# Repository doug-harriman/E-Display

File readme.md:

# TO-DO

Updated: 2026-02-01

- [ ] Authentication through web page has not been updated for MSAL.

# Electronic Image Display Server

Image server for remote electronic displays such as a Kindle.

The image below shows my two devices, one displaying my work calendar in a portrait orientation, the other displaying the family calendar for the week in landscape.

|Server Pages|||
|-|-|-|
|||
|||

## Motivation

This project was motivated by two desires:
1. To have a nice display of my work calendar on my desk, available at a glance without having to open up Outlook.
2. To learn about web programming via Python.

I know there's a lot of stuff here that could be greatly improved.  Please submit pull requests if you'd like to help.

## Project Inspiration & References

There are many impressive projects out there that do similar things.  They've both inspired this project and provided great references for technical implementations.  Some great projects to check out:

* [Matt Healy's](https://matthealy.com/kindle) project was the one that originally inspired me.
    * I preferred to directly generate images for specific devices rather than generate web pages then convert to images.
    * He provides great instructions for the install process.  Great overview.
    * I'm still working on getting a frame like he has.
* A cuple of weather display projects that I really liked due to their use of weather icons:
    * [Weather Display](https://mpetroff.net/2012/09/kindle-weather-display/)
    * [Kindle Weather](https://github.com/DDRBoxman/kindle-weather)
        * SVG Files for weather icons, fonts too.
        * [Great example of managing Kindle services](https://github.com/DDRBoxman/kindle-weather/blob/master/kindleweather.sh).
* [A wall paper project](https://github.com/pablojimenezmateo/kindle-wallpaper)
    * Dumps the image file into the screensaver and reboots.
    * Sets a cron job to generate a new screen saver image once per day.
    * SVG files for weather icons.
* Two projects that dive deeper into reducing Kindle power usage:
    * [One with full power saving](https://github-com.translate.goog/nicoh88/kindle-kt3_weatherdisplay_battery-optimized?_x_tr_sl=auto&_x_tr_tl=en&_x_tr_hl=en)
    * [Another with power saving](https://www.martinpham.com/2023/01/07/reviving-unused-kindle-ebooks/)
* [A list of other Kindle projects from Mobileread](https://www.mobileread.com/forums/showthread.php?t=128704&highlight=wake+sleep+command).

## Key System Features

* Image generation performed on server to keep display device code as simple as possible.  This also allows for easy updates to the display without having to update the device.
* Server code constructed to support multiple display devices, so only a single server is needed.
* Display device can request sleep time from server, so that it can go into low power mode.  This allows the server to have complex logic to determine sleep duration based on a variety of factors.  I use it to reduce my work calendar display refresh rate during non-work hours.
    * Images are be pre-generated just ahead of wake time so that they're ready without wait mimimizing device battery usage.
* Display device can send basic state information (battery state of charge and local temperature) to server which is stored in an [SQLite3](https://www.sqlite.org/index.html) database.  State information can then be used for image generation.
* Server code constructed to support plugins, so features can be added easily and auto-discovered.

### Feature Details
* High-res image generation via [Pillow](https://pillow.readthedocs.io/en/stable/).
* Reusable image header and footer.
    * Header
        * Current day of week, month and date.
        * Battery state of charge.
    * Footer
        * Last update time (last time image was generated on server).
        * Device IP address.
        * Device name.
* Weather
    * Query weather forecast from USA National Weather Service.
    * Map weather forecast to icons.
* Google Calendar
    * Query events
    * Generate one week calendar image.
    * Select which of your Google calendars to display.
* Microsoft Outlook 365 Calendar
    * Query events
    * Generate hour by hour event image for the current day.
    * Display hour by hour weather forecast.
    * Request authentication URL from the web page, and apply the URL.  By default, some Outlook setups required admin approval for access longer than 24 hours.  This simplifies daily re-authentication.
* Custom string filters to remove unwanted text from event subjects for cleaner display.
* Display properties for Kindle Paperwhite
    * Screen resolution & size
    * Color maps (grayscale)
    * Fonts
* HTTP Post to MQTT Bridge
    * Post state information to MQTT broker.
    * Keeps device software simple.  MQTT data stream without adding MQTT client to device.
    * Additional small MQTT process to push MQTT data to Influx DB.
* Server software updates via `git pull` from direcltly from web server.

## Installation

The server should be set up and running before setting up the devices.  The devices will expect the server to be available so that they can pull images from it.

### Server

Installation and configuration for the server are covered in the [Server](server/readme.md) documentation.

### Kindle

Installation and configuration for using Kindle Paperwhite devices for an E-Display are covered in the [Kindle](kindle/readme.md) documentation.

## Creating a New Device Image

## Creating a New Plugin

## Next Tasks

- [ ] Server: Move all config/credential files to a single directory.
    - This would make it easier to sync files to the server.
    - Could then provide an upload/download functionality.
- [ ] Server: Family calendar image weather added
- [ ] Server: Review TODO's
- [ ] Server: Retrieve google cal events with async to speed up download of multiple calendars.
    - Google cal asyncio: https://pypi.org/project/aiogc/
    - Gathering results: https://superfastpython.com/asyncio-gather/#:~:text=main%20done-,Example%20of%20gather()%20With%20Return%20Values,-We%20may%20execute
- [ ] Server: Log to file.
- [ ] Server: renderer base should accept a layout parameter (landscape, portrait) and then manage resolution and image rotation internally.
- [ ] Server: Containerize to Docker.
- [ ] Server: Make MQTT2InfluxDB a daemon and run on container.
- [ ] Server: Icon updates.
    - Would be nice to have a battery outline icon to better match the weather icons.
    - During initial icon search, had trouble finding good SVG sets.  After battery icon was implemented found [Icônes](https://icones.js.org/), which has a lot of really good looking options.
        - From there, these look like good battery icon options:
            - https://icones.js.org/collection/mingcute?s=battery
            - https://icones.js.org/collection/typcn?s=battery
        - Potential weather changes
            - https://icones.js.org/collection/mdi?s=weather
            - https://icones.js.org/collection/uil?s=cloud

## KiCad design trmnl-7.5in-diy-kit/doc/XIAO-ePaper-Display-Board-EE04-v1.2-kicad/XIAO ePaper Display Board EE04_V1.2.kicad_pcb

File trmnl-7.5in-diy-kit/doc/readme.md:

# TRMNL 7.5" DIY Kit

## PCA Connections

## Reseting

To force a reset, hold the microswitch on the ESP daughterboard while pressing the reset button on the main board. There are two microswitches on the daughterboard.  The one for boot is closer to the battery plug.

## Links

* [Firmware GitHub](https://github.com/Seeed-Projects/Seeed_TRMNL_Eink_Project)
* [SEEED Studio Page](https://wiki.seeedstudio.com/trmnl_7inch5_diy_kit_main_page/)
* [SEEED Studio EE04 Display Board Page](https://wiki.seeedstudio.com/epaper_ee04/)
* [Overview Blog](https://www.seeedstudio.com/blog/2025/09/19/build-your-own-custom-e-ink-display-with-the-trmnl-diy-kit/)
* 3D Printed Enclosure Designs
   * [Triangular](https://www.printables.com/model/1354873-triangular-prism-3d-enclosure-for-trmnl-75-og-diy)
   * [L-Shaped](https://www.printables.com/model/1354879-l-shape-3d-enclosure-for-trmnl-75-og-diy-kit)

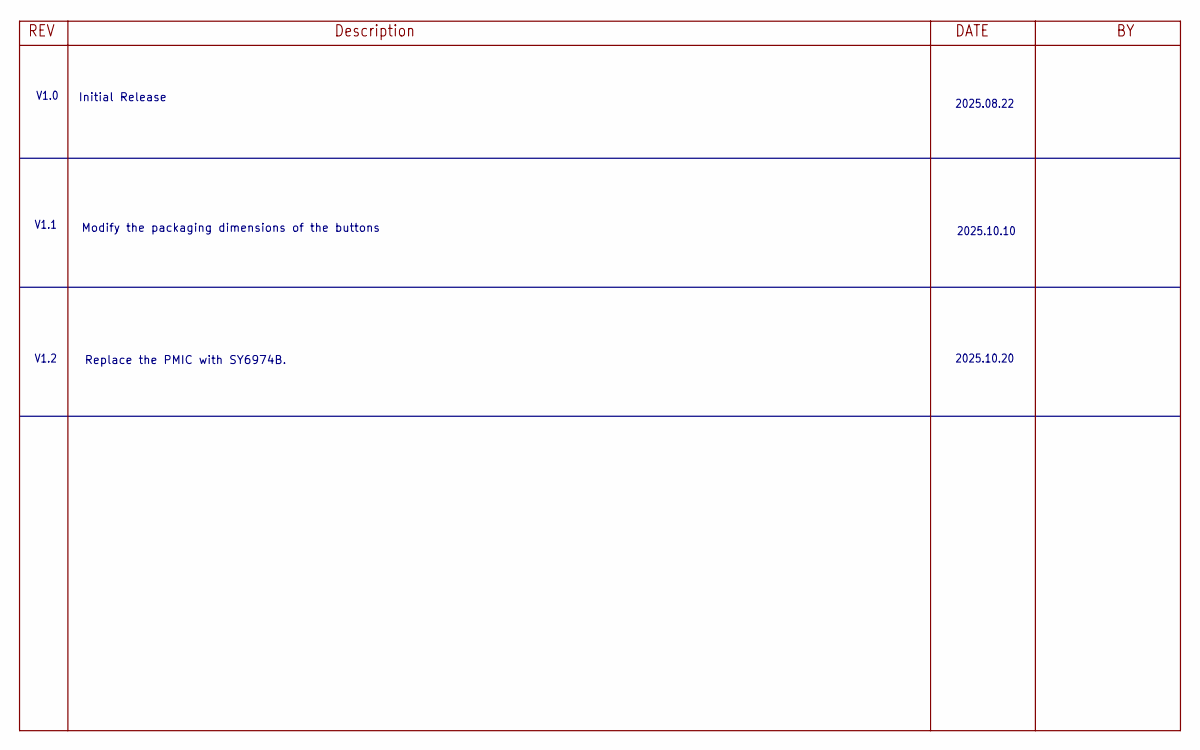
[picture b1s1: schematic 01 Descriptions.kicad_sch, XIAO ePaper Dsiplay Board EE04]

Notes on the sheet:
2025.08.22
2025.10.20
2025.10.10
Modify the packaging dimensions of the buttons
Replace the PMIC with SY6974B.
V1.1
Initial Release
V1.0
V1.2

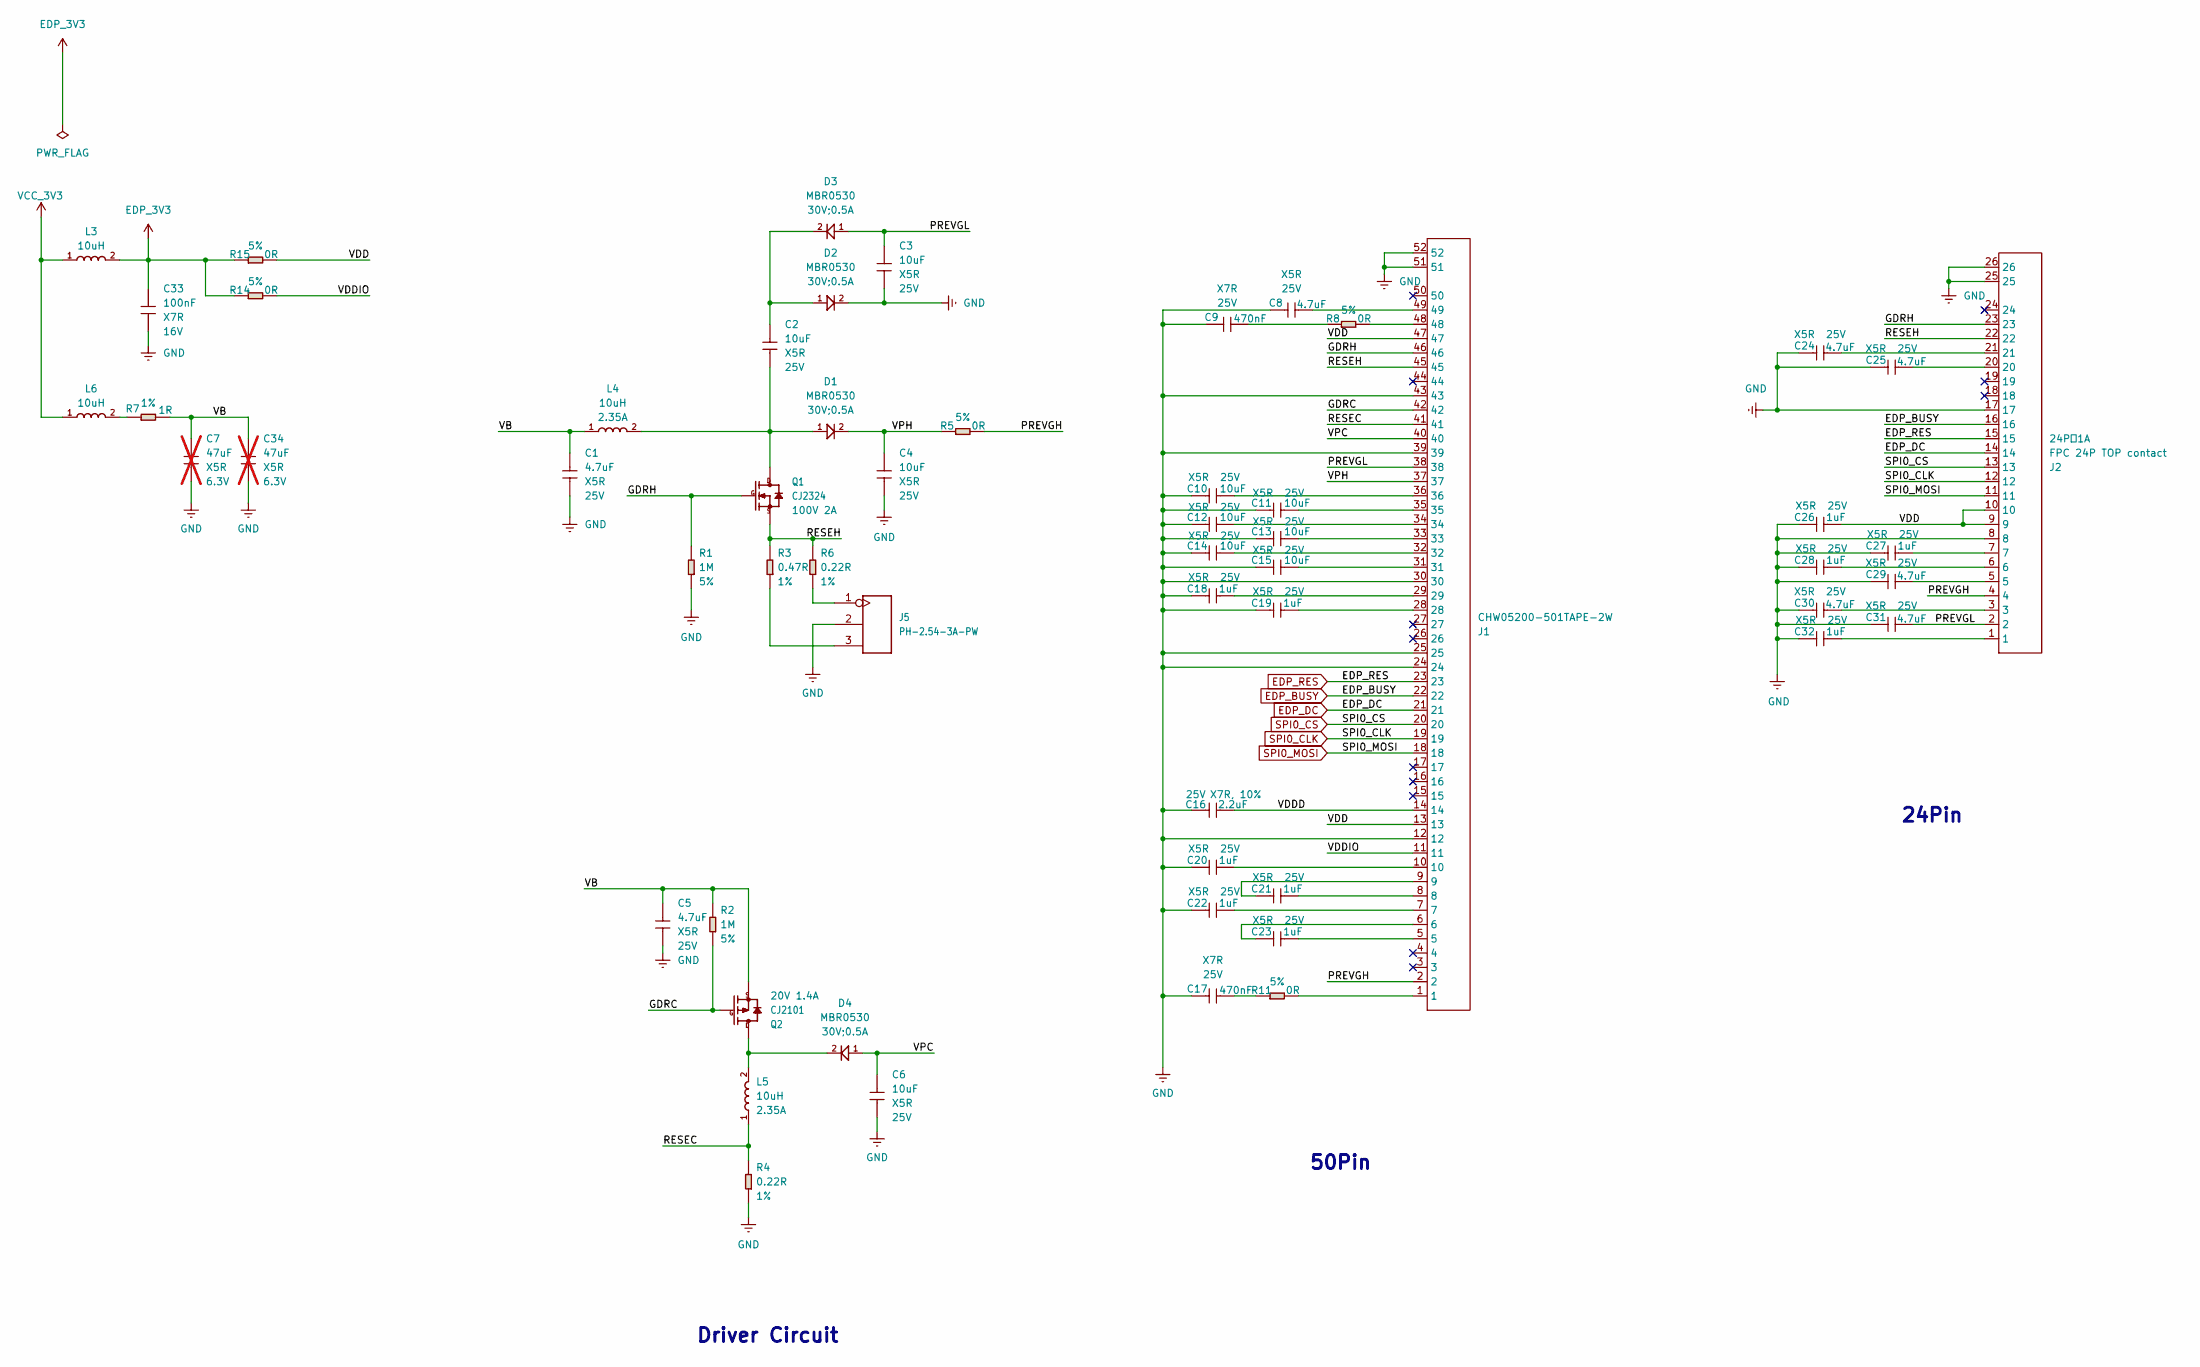
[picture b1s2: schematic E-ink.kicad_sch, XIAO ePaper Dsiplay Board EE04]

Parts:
C1, C5, C8, C24, C25, C29, C30, C31: 4.7uF; C0805; Voltage Rating 25V; MPN CC0805KKX5R8BB475
C2, C3, C4, C6, C10, C11, C12, C13, C14, C15: 10uF; C0805; Voltage Rating 25V; MPN CC0805KKX5R8BB106
C7, C34: 47uF; C0805; Voltage Rating 6.3V; MPN CC0805MKX5R5BB476; not fitted
C9, C17: 470nF; C0603; Voltage Rating 25V; MPN CC0603KRX7R8BB474
C16: 2.2uF; C0805; Voltage Rating 25V; MPN CC0805KKX7R8BB225
C18, C19, C20, C21, C22, C23, C26, C27, C28, C32: 1uF; C0402; Voltage Rating 25V; MPN CC0402KRX5R8BB105
C33: 100nF; C0402; Voltage Rating 16V; MPN CC0402KRX7R7BB104
D1, D2, D3, D4: MBR0530; SOD-123; Rating 30V;0.5A; MPN MBR0530
J1: CHW05200-501TAPE-2W; FPC50-0.5-28.6X4.9X2MM; MPN CHW05200-501TAPE-2W
J2: FPC 24P TOP contact; FPC24-0.5-15.5X4.9X2MM; Rating 24P，1A; MPN FPC0.5K-DH-24WB
J5: PH-2.54-3A-PW; H3-2.54-90D; MPN PH-2.54-3A-PW
L3, L6: 10uH; L0603; MPN MWSD1608FE100KT
L4, L5: 10uH; L5040S; Rating 2.35A; MPN SWPA5040S100MT
Q1: CJ2324; SOT23; Rating 100V 2A; MPN CJ2324
Q2: CJ2101; SOT-323; Rating 20V 1.4A; MPN CJ2101
R1, R2: 1M; R0402; Power Rating 5%; MPN RC0402JR-071ML
R3: 0.47R; R0603; Power Rating 1%; MPN RL0603FR-070R47L
R4, R6: 0.22R; R0805; Power Rating 1%; MPN RL0805FR-7W0R22L
R5, R8, R11, R14, R15: 0R; R0603; Power Rating 5%; MPN RC0603JR-070RL
R7: 1R; R0805; Power Rating 1%; MPN RC0805FR-071RL

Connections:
/E-ink/GDRC: J1.42, Q2.1 (G), R2.1
/E-ink/GDRH: J1.46, J2.23, Q1.1 (G), R1.2
/E-ink/PREVGH: J1.2, J2.4, R5.2
/E-ink/PREVGL: C3.2, C31.2, D3.1, J1.38, J2.2
/E-ink/RESEC: J1.41, L5.1, R4.2
/E-ink/RESEH: J1.45, J2.22, Q1.2 (S), R3.2, R6.2
/E-ink/VB: C1.1, C5.1, C7.1, C34.1, L4.1, Q2.2 (S), R2.2, R7.2
/E-ink/VDD: C26.2, J1.13, J1.47, J2.9, J2.10, R15.2
/E-ink/VDDD: C16.2, J1.14
/E-ink/VDDIO: J1.11, R14.2
/E-ink/VPC: C6.2, D4.1, J1.40
/E-ink/VPH: C4.2, D1.2, J1.37, R5.1
EDP_3V3: C33.1, L3.2, R14.1, R15.1
EDP_BUSY: J1.22, J2.16; also elsewhere on the board
EDP_DC: J1.21, J2.14; also elsewhere on the board
EDP_RES: J1.23, J2.15; also elsewhere on the board
GND: C1.2, C3.1, C4.1, C5.2, C6.1, C7.2, C8.1, C9.1, C10.2, C11.2, C12.2, C13.2, C14.2, C15.2, C16.1, C17.1, C18.1, C19.1, C20.1, C22.1, C24.1, C25.1, C26.1, C27.1, C28.1, C29.1, C30.1, C31.1, C32.1, C33.2, C34.2, D2.2, J1.12, J1.24, J1.25, J1.30, J1.39, J1.43, J1.51, J1.52, J2.8, J2.17, J2.25, J2.26, J5.2, R1.1, R4.1; also elsewhere on the board
unnamed: C2.2, D2.1, D3.2
unnamed: C8.2, J1.49
unnamed: C9.2, R8.1
unnamed: C10.1, J1.36
unnamed: C11.1, J1.35
unnamed: C12.1, J1.34
unnamed: C13.1, J1.33
unnamed: C14.1, J1.32
unnamed: C15.1, J1.31
unnamed: C17.2, R11.1
unnamed: C18.2, J1.29
unnamed: C19.2, J1.28
unnamed: C20.2, J1.10
unnamed: C21.1, J1.9
unnamed: C21.2, J1.8
unnamed: C22.2, J1.7
unnamed: C23.1, J1.6
unnamed: C23.2, J1.5
unnamed: C24.2, J2.21
unnamed: C25.2, J2.20
unnamed: C27.2, J2.7
unnamed: C28.2, J2.6
unnamed: C29.2, J2.5
unnamed: C30.2, J2.3
unnamed: C32.2, J2.1
unnamed: J1.1, R11.2
unnamed: J1.48, R8.2
unnamed: J5.1, R6.1
unnamed: J5.3, R3.1
unnamed: L6.2, R7.1
unnamed: C2.1, D1.1, L4.2, Q1.3 (D)
unnamed: D4.2, L5.2, Q2.3 (D)
SPI0_CLK: J1.19, J2.12; also elsewhere on the board
SPI0_CS: J1.20, J2.13; also elsewhere on the board
SPI0_MOSI: J1.18, J2.11; also elsewhere on the board
VCC_3V3: L3.1, L6.1; also elsewhere on the board

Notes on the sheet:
Driver Circuit
24Pin
50Pin

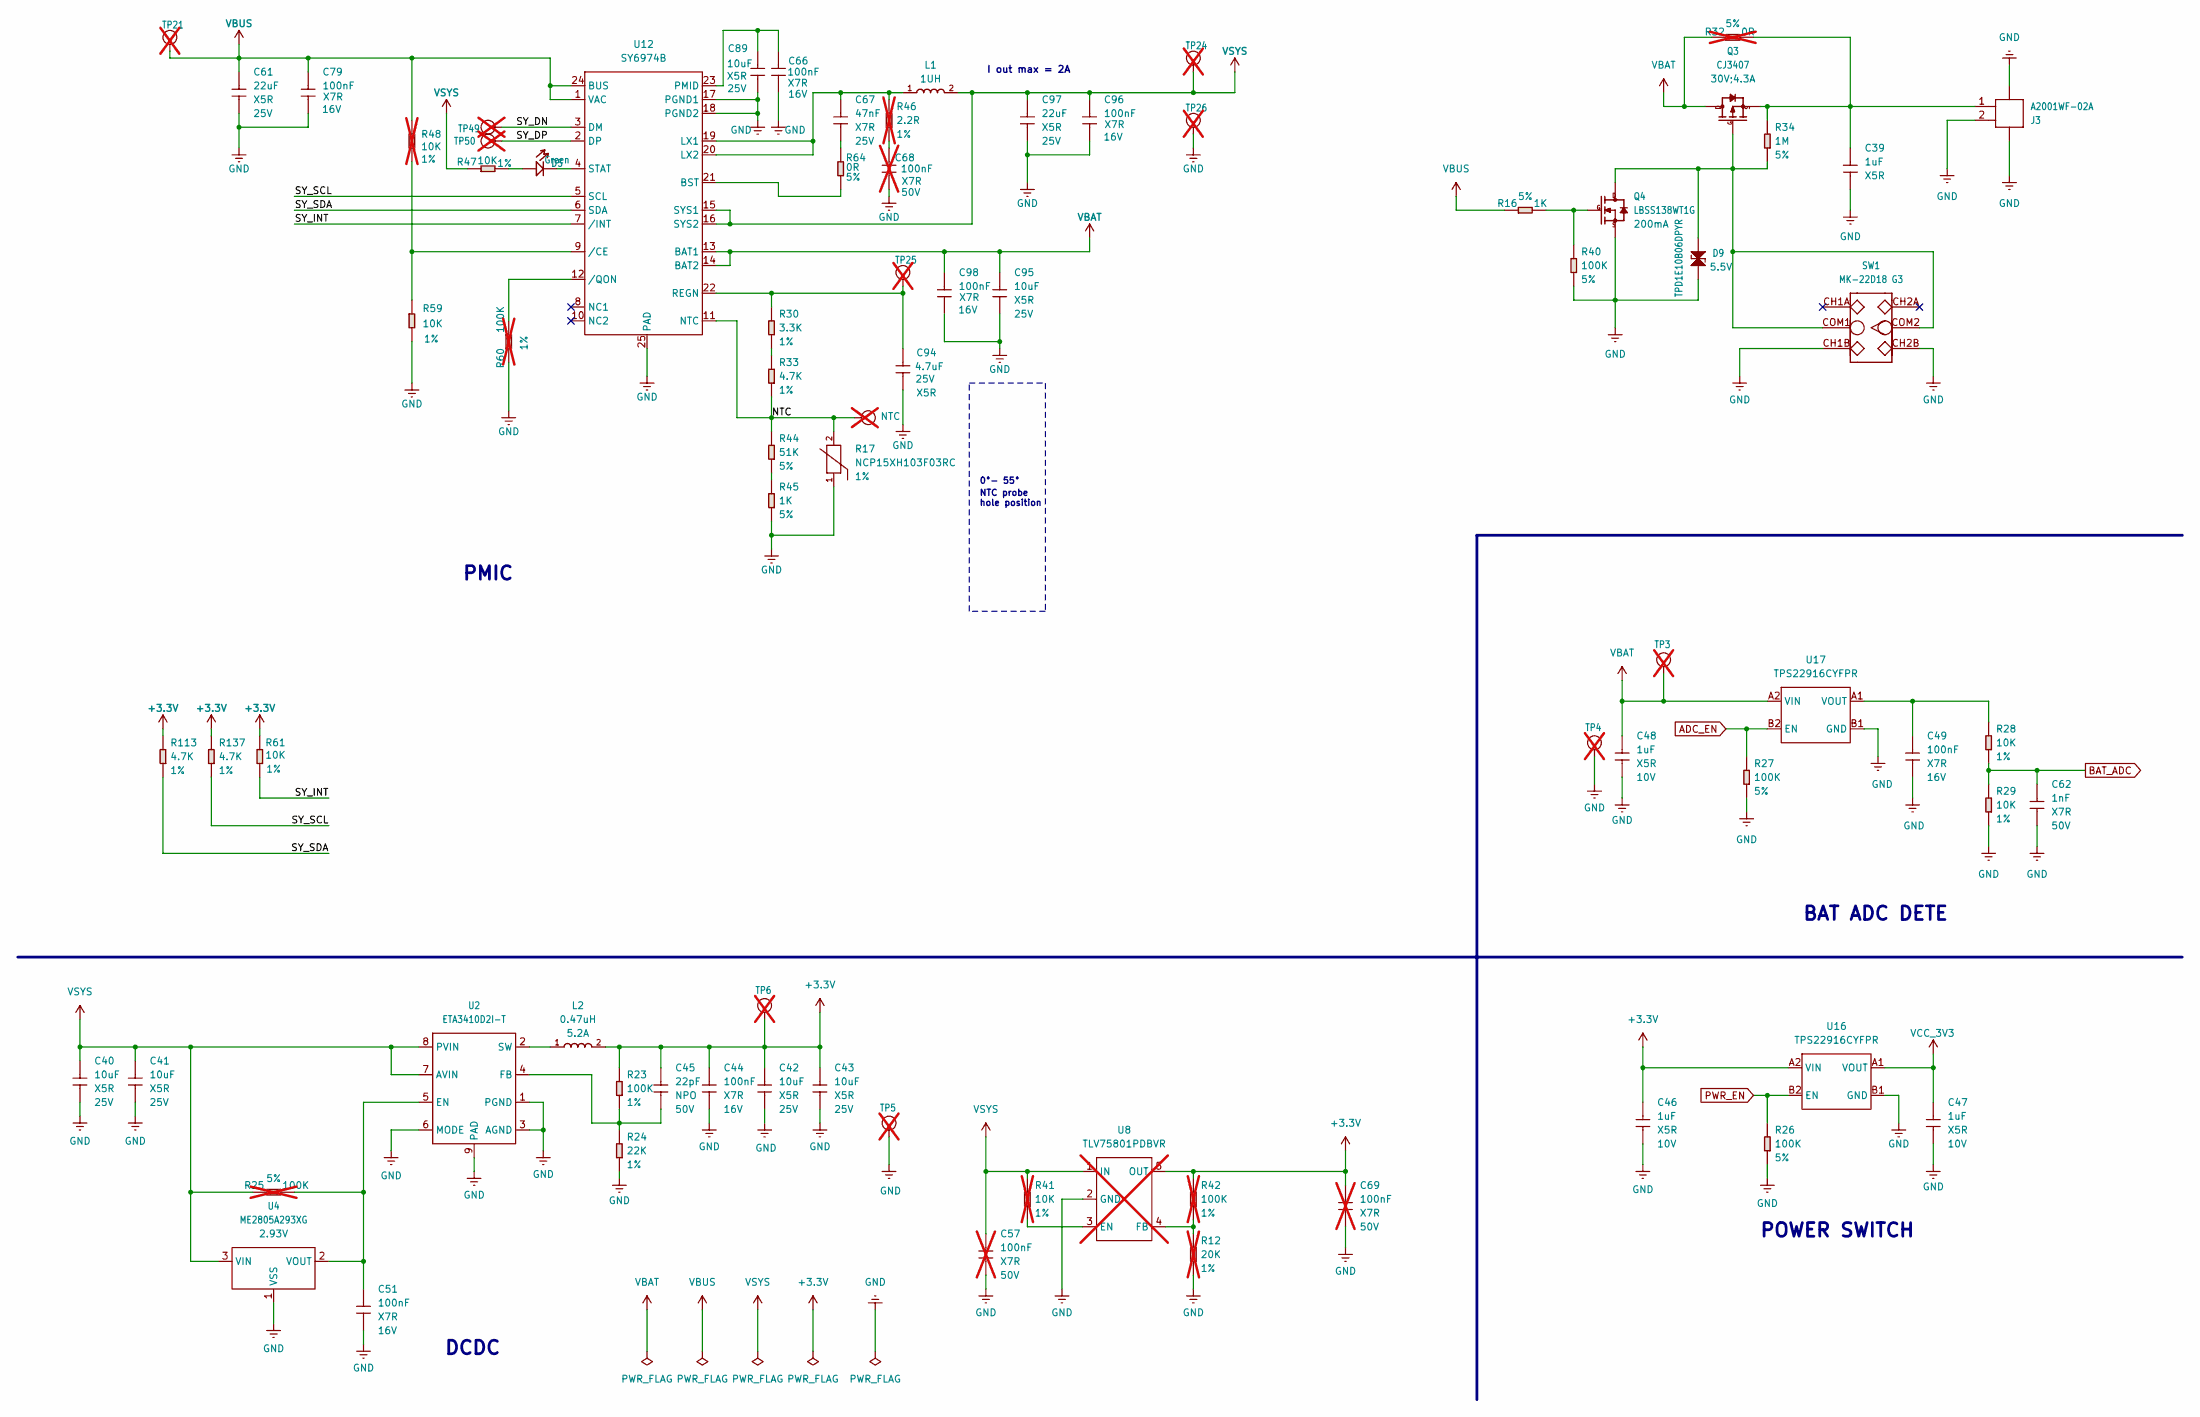
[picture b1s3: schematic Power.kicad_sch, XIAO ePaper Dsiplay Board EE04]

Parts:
C39, C46, C47, C48: 1uF; C0402; Voltage Rating 10V; MPN CC0402KRX5R6BB105
C40, C41, C42, C43, C89, C95: 10uF; C0805; Voltage Rating 25V; MPN CC0805KKX5R8BB106
C44, C49, C51, C66, C79, C96, C98: 100nF; C0402; Voltage Rating 16V; MPN CC0402KRX7R7BB104
C45: 22pF; C0402; Voltage Rating 50V; MPN CC0402JRNPO9BN220
C57, C68, C69: 100nF; C0603; Voltage Rating 50V; MPN CC0603KRX7R9BB104; not fitted
C61, C97: 22uF; C0805; Voltage Rating 25V; MPN CC0805MKX5R8BB226
C62: 1nF; C0402; Voltage Rating 50V; MPN CC0402KRX7R9BB102
C67: 47nF; C0402; Voltage Rating 25V; MPN CC0402KRX7R8BB473
C94: 4.7uF; C0805; Voltage Rating 25V; MPN CC0805KKX5R8BB475
D5: Green; LED2-0.6X1.7MM; MPN 27-21/GHC-YR1S2M/3C
D9: TPD1E10B06DPYR; ESD-0402; Rating 5.5V; MPN TPD1E10B06DPYR
J3: A2001WF-02A; JST2+2P_2.0_PH_S2B-PH-SM4-TB_1x02-1MP_Horizontal; MPN A2001WF-02A
L1: 1UH; INT2-SMD-4.2X4.4X1.8MM; MPN MWSA0402S-1R0MT
L2: 0.47uH; L0805; Rating 5.2A; MPN WPN201610MR47MT
NTC_IN2: NTC; TP-D45MIL; Part Type Test Point; not fitted
Q3: CJ3407; SOT23; Rating 30V;4.3A; MPN CJ3407
Q4: LBSS138WT1G; SOT-323; Rating 200mA; MPN LBSS138WT1G
R12: 20K; R0402; Power Rating 1%; MPN RC0402FR-0720KL; not fitted
R16, R45: 1K; R0402; Power Rating 5%; MPN RC0402JR-071KL
R17: NCP15XH103F03RC; R0402; Power Rating 1%; MPN NCP15XH103F03RC
R23: 100K; R0402; Power Rating 1%; MPN RC0402FR-07100KL
R24: 22K; R0402; Power Rating 1%; MPN RC0402FR-0722KL
R25: 100K; R0402; Power Rating 5%; MPN RC0402JR-07100KL; not fitted
R26, R27, R40: 100K; R0402; Power Rating 5%; MPN RC0402JR-07100KL
R28, R29, R47, R59, R61: 10K; R0402; Power Rating 1%; MPN RC0402FR-0710KL
R30: 3.3K; R0402; Power Rating 1%; MPN RC0402JR-073K3L
R32: 0R; R0603; Power Rating 5%; MPN RC0603JR-070RL; not fitted
R33, R113, R137: 4.7K; R0402; Power Rating 1%; MPN RC0402FR-074K7L
R34: 1M; R0402; Power Rating 5%; MPN RC0402JR-071ML
R41, R48: 10K; R0402; Power Rating 1%; MPN RC0402FR-0710KL; not fitted
R42, R60: 100K; R0402; Power Rating 1%; MPN RC0402FR-07100KL; not fitted
R44: 51K; R0402; Power Rating 5%; MPN RC0402JR-0751KL
R46: 2.2R; R0603; Power Rating 1%; MPN RC0603FR-072R2L; not fitted
R64: 0R; R0402; Power Rating 5%; MPN RC0402JR-070RL
SW1: MK-22D18 G3; SW6-2CH-2.54-9X3.5X3.5; MPN MK-22D18 G3
TP3, TP4, TP5, TP6, TP21, TP24, TP25, TP26, TP49, TP50: Test Point; TP-D45MIL; Part Type Test Point; not fitted
U2: ETA3410D2I-T; DFN8G-0.5-2X2MM; MPN ETA3410D2I-T
U4: ME2805A293XG; SOT-23; Rating 2.93V; MPN ME2805A293XG
U8: TLV75801PDBVR; SOT-23-5; MPN TLV75801PDBVR; not fitted
U12: SY6974B; QFN24G-0.5-4X4MM; MPN SY6974B
U16, U17: TPS22916CYFPR; WLCSP4-0.4-0.77X0.77X0.33MM; MPN TPS22916CYFPR

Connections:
+3.3V: C42.2, C43.2, C44.1, C45.1, C46.1, C69.1, L2.2, R23.2, R42.2, R61.2, R113.2, R137.2, TP6.1 (T), U8.5 (OUT), U16.A2 (VIN)
/Power/NTC: NTC_IN2.1 (T), R17.2, R33.1, R44.2, U12.11 (NTC)
/Power/SY_DN: TP49.1 (T), U12.3 (DM)
/Power/SY_DP: TP50.1 (T), U12.2 (DP)
/Power/SY_INT: R61.1, U12.7 (/INT)
/Power/SY_SCL: R137.1, U12.5 (SCL)
/Power/SY_SDA: R113.1, U12.6 (SDA)
ADC_EN: R27.2, U17.B2 (EN); also elsewhere on the board
BAT_ADC: C62.1, R28.1, R29.2; also elsewhere on the board
GND: C39.2, C40.1, C41.1, C42.1, C43.1, C44.2, C46.2, C47.2, C48.2, C49.2, C51.2, C57.2, C61.2, C62.2, C66.1, C68.1, C69.2, C79.2, C89.1, C94.2, C95.2, C96.2, C97.2, C98.2, D9.1, J3.2, J3.3, J3.4, Q4.2 (S), R12.1, R17.1, R24.1, R26.1, R27.1, R29.1, R40.1, R45.1, R59.2, R60.2, SW1.CH1B, SW1.CH2B, TP4.1 (T), TP5.1 (T), TP26.1 (T), U2.1 (PGND), U2.3 (AGND), U2.6 (MODE), U2.9 (PAD), U4.1 (VSS), U8.2 (GND), U12.17 (PGND1), U12.18 (PGND2), U12.25 (PAD), U16.B1 (GND), U17.B1 (GND); also elsewhere on the board
unnamed: C67.2, R64.2
unnamed: C68.2, R46.1
unnamed: D5.1 (+), R47.2
unnamed: D5.2 (-), U12.4 (STAT)
unnamed: D9.2, Q3.1 (G), Q4.3 (D), R34.1, SW1.COM1, SW1.COM2
unnamed: C39.1, J3.1, Q3.2 (S), R32.2, R34.2
unnamed: Q4.1 (G), R16.2, R40.2
unnamed: R30.1, R33.2
unnamed: R44.1, R45.2
unnamed: C94.1, R30.2, TP25.1 (T), U12.22 (REGN)
unnamed: C51.1, R25.1, U2.5 (EN), U4.2 (VOUT)
unnamed: C45.2, R23.1, R24.2, U2.4 (FB)
unnamed: L2.1, U2.2 (SW)
unnamed: R41.1, U8.3 (EN)
unnamed: R12.2, R42.1, U8.4 (FB)
unnamed: R64.1, U12.21 (BST)
unnamed: C67.1, L1.1, R46.2, U12.19 (LX1), U12.20 (LX2)
unnamed: C66.2, C89.2, U12.23 (PMID)
unnamed: R48.1, R59.1, U12.9 (/CE)
unnamed: R60.1, U12.12 (/QON)
unnamed: C49.1, R28.2, U17.A1 (VOUT)
PWR_EN: R26.2, U16.B2 (EN); also elsewhere on the board
VBAT: C48.1, C95.1, C98.1, Q3.3 (D), R32.1, TP3.1 (T), U12.13 (BAT1), U12.14 (BAT2), U17.A2 (VIN); also elsewhere on the board
VBUS: C61.1, C79.1, R16.1, R48.2, TP21.1 (T), U12.1 (VAC), U12.24 (BUS); also elsewhere on the board
VCC_3V3: C47.1, U16.A1 (VOUT); also elsewhere on the board
VSYS: C40.2, C41.2, C57.1, C96.1, C97.1, L1.2, R25.2, R41.2, R47.1, TP24.1 (T), U2.7 (AVIN), U2.8 (PVIN), U4.3 (VIN), U8.1 (IN), U12.15 (SYS1), U12.16 (SYS2)

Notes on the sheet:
PMIC
DCDC
BAT ADC DETE
POWER SWITCH
0°- 55°
I out max = 2A
NTC probe hole position

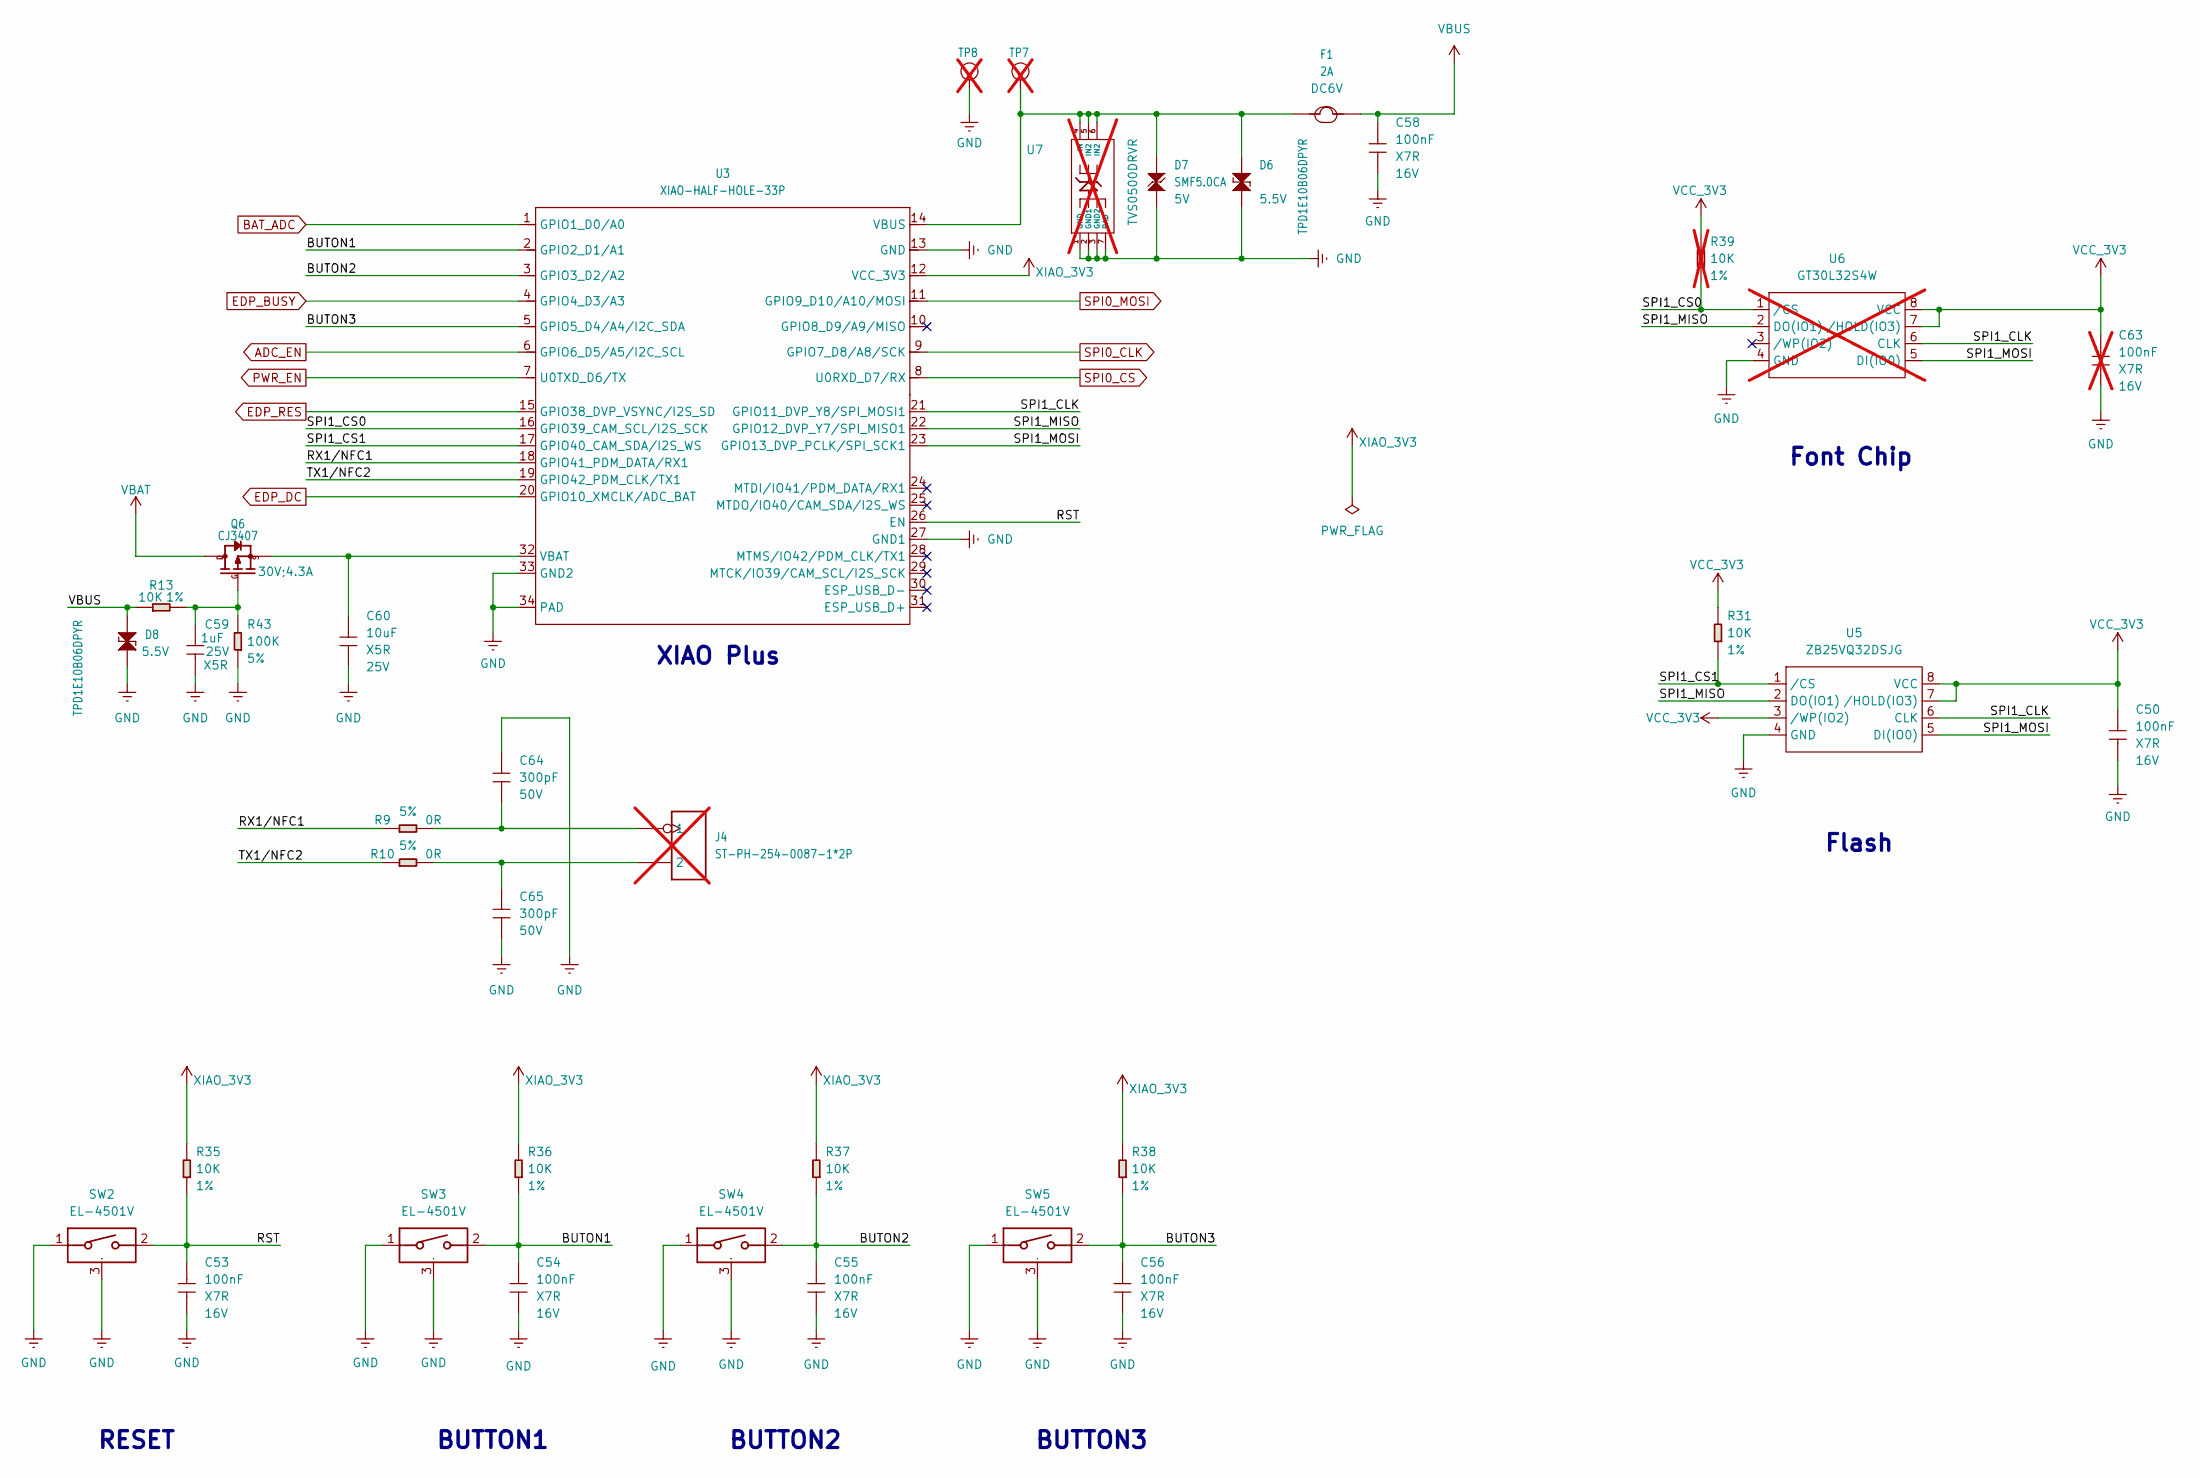
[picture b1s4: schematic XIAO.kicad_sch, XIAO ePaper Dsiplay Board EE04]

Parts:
C50, C53, C54, C55, C56, C58: 100nF; C0402; Voltage Rating 16V; MPN CC0402KRX7R7BB104
C59: 1uF; C0402; Voltage Rating 25V; MPN CC0402KRX5R8BB105
C60: 10uF; C0805; Voltage Rating 25V; MPN CC0805KKX5R8BB106
C63: 100nF; C0402; Voltage Rating 16V; MPN CC0402KRX7R7BB104; not fitted
C64, C65: 300pF; C0402; Voltage Rating 50V; MPN GRM1555C1H301JA01D
D6, D8: TPD1E10B06DPYR; ESD-0402; Rating 5.5V; MPN TPD1E10B06DPYR
D7: SMF5.0CA; SOD-123; Rating 5V; MPN SMF5.0CA
F1: 2A; F1210; Rating DC6V; MPN SMD1210R200SF
J4: ST-PH-254-0087-1*2P; H2P-2.54-65_40MIL; MPN ST-PH-254-0087-1*2P; not fitted
Q6: CJ3407; SOT23; Rating 30V;4.3A; MPN CJ3407
R9, R10: 0R; R0402; Power Rating 5%; MPN RC0402JR-070RL
R13, R31, R35, R36, R37, R38: 10K; R0402; Power Rating 1%; MPN RC0402FR-0710KL
R39: 10K; R0402; Power Rating 1%; MPN RC0402FR-0710KL; not fitted
R43: 100K; R0402; Power Rating 5%; MPN RC0402JR-07100KL
SW2, SW3, SW4, SW5: EL-4501V; SW3-DIP-SIDE-4.5X4.5X5.5MM; MPN EL-4501V
TP7, TP8: Test Point; TP-D45MIL; Part Type Test Point; not fitted
U3: XIAO-HALF-HOLE-33P; XIAO-ESP32-S3-Plus-SMD
U5: ZB25VQ32DSJG; SOIC8-1.27-5.3X5.3MM; MPN ZB25VQ32DSJG
U6: GT30L32S4W; SOP8-1.27-5.2X5.2x2.16MM; MPN GT30L32S4W; not fitted
U7: TVS0500DRVR; WSON7-0.65-2X2X0.8MM; MPN TVS0500DRVR; not fitted

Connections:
/XIAO/BUTON1: C54.1, R36.1, SW3.2, U3.2 (GPIO2_D1/A1)
/XIAO/BUTON2: C55.1, R37.1, SW4.2, U3.3 (GPIO3_D2/A2)
/XIAO/BUTON3: C56.1, R38.1, SW5.2, U3.5 (GPIO5_D4/A4/I2C_SDA)
/XIAO/RST: C53.1, R35.1, SW2.2, U3.26 (EN)
/XIAO/RX1/NFC1: R9.1, U3.18 (GPIO41_PDM_DATA/RX1)
/XIAO/SPI1_CLK: U3.21 (GPIO11_DVP_Y8/SPI_MOSI1), U5.6 (CLK), U6.6 (CLK)
/XIAO/SPI1_CS0: R39.1, U3.16 (GPIO39_CAM_SCL/I2S_SCK), U6.1 (/CS)
/XIAO/SPI1_CS1: R31.1, U3.17 (GPIO40_CAM_SDA/I2S_WS), U5.1 (/CS)
/XIAO/SPI1_MISO: U3.22 (GPIO12_DVP_Y7/SPI_MISO1), U5.2 (DO(IO1)), U6.2 (DO(IO1))
/XIAO/SPI1_MOSI: U3.23 (GPIO13_DVP_PCLK/SPI_SCK1), U5.5 (DI(IO0)), U6.5 (DI(IO0))
/XIAO/TX1/NFC2: R10.1, U3.19 (GPIO42_PDM_CLK/TX1)
ADC_EN: U3.6 (GPIO6_D5/A5/I2C_SCL); also elsewhere on the board
BAT_ADC: U3.1 (GPIO1_D0/A0); also elsewhere on the board
EDP_BUSY: U3.4 (GPIO4_D3/A3); also elsewhere on the board
EDP_DC: U3.20 (GPIO10_XMCLK/ADC_BAT); also elsewhere on the board
EDP_RES: U3.15 (GPIO38_DVP_VSYNC/I2S_SD); also elsewhere on the board
GND: C50.2, C53.2, C54.2, C55.2, C56.2, C58.2, C59.2, C60.1, C63.2, C64.1, C65.2, D6.1, D7.1, D8.1, R43.1, SW2.1, SW2.3 (GND), SW3.1, SW3.3 (GND), SW4.1, SW4.3 (GND), SW5.1, SW5.3 (GND), TP8.1 (T), U3.13 (GND), U3.27 (GND1), U3.33 (GND2), U3.34 (PAD), U5.4 (GND), U6.4 (GND), U7.1 (GND), U7.2 (GND1), U7.3 (GND2), U7.7 (PAD); also elsewhere on the board
unnamed: C64.2, J4.1, R9.2
unnamed: C65.1, J4.2, R10.2
unnamed: C59.1, Q6.1 (G), R13.2, R43.2
unnamed: C60.2, Q6.2 (S), U3.32 (VBAT)
unnamed: D6.2, D7.2, F1.1, TP7.1 (T), U3.14 (VBUS), U7.4 (IN), U7.5 (IN2), U7.6 (IN2)
PWR_EN: U3.7 (U0TXD_D6/TX); also elsewhere on the board
SPI0_CLK: U3.9 (GPIO7_D8/A8/SCK); also elsewhere on the board
SPI0_CS: U3.8 (U0RXD_D7/RX); also elsewhere on the board
SPI0_MOSI: U3.11 (GPIO9_D10/A10/MOSI); also elsewhere on the board
VBAT: Q6.3 (D); also elsewhere on the board
VBUS: C58.1, D8.2, F1.2, R13.1; also elsewhere on the board
VCC_3V3: C50.1, C63.1, R31.2, R39.2, U5.3 (/WP(IO2)), U5.7 (/HOLD(IO3)), U5.8 (VCC), U6.7 (/HOLD(IO3)), U6.8 (VCC); also elsewhere on the board
XIAO_3V3: R35.2, R36.2, R37.2, R38.2, U3.12 (VCC_3V3)

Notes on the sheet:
BUTTON1
BUTTON2
Flash
BUTTON3
Font Chip
RESET
XIAO Plus

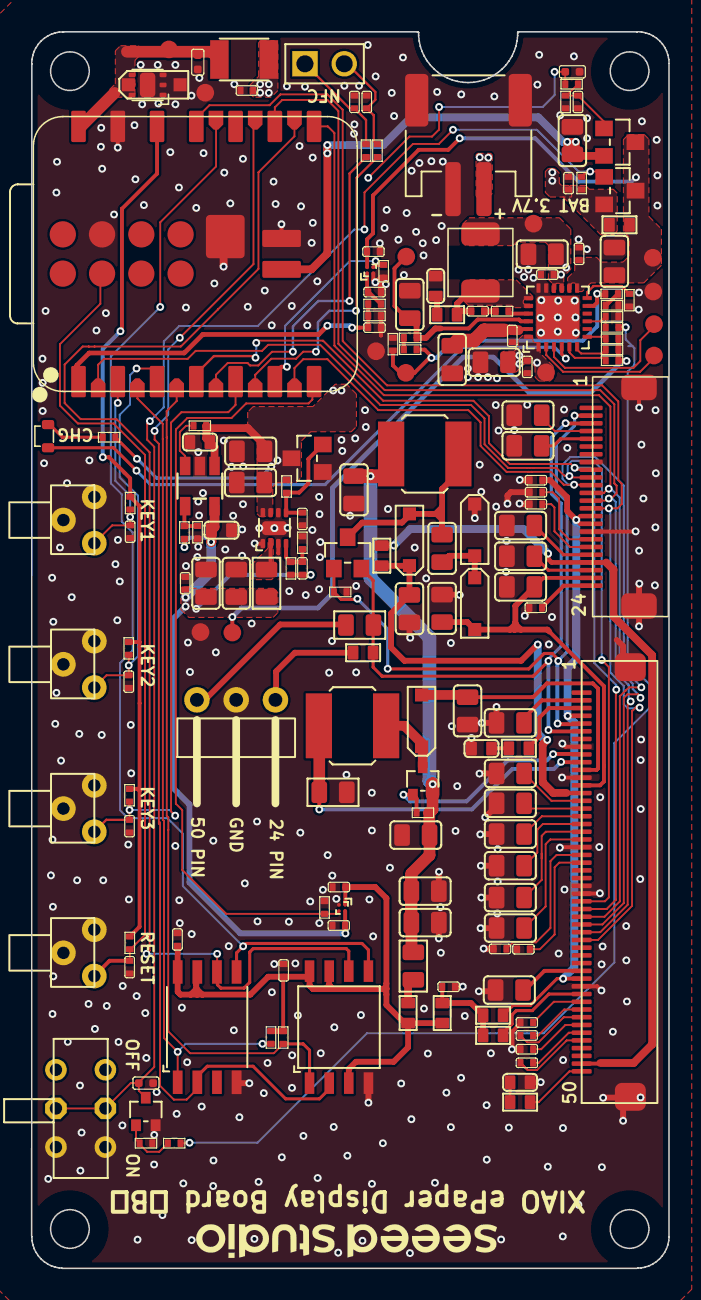
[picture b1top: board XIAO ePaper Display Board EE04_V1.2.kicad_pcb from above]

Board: 2 copper layers, 41.2 x 80.0 mm, 174 parts (0 on the bottom side), 104 nets.

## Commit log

2023-08-05 Doc updates. Requirements.txt added.
2023-08-05 Better file tree rendering.
2023-08-05 Added image of Kindles.
2023-08-06 Fix regular expression issue.
2023-08-06 Add server screenshots.
2023-08-06 Added images of server pages.
2023-08-06 Update function documentation.
2023-08-06 Drop "Kindle" from web pages.
2023-08-06 Documentation updates.
2023-08-06 Kindle init script updates.
2023-08-06 More documentation updates.
2023-08-06 Moving issues to github issue tracker.
2023-08-06 Server config doc started.
2023-08-06 doc update
2023-08-10 Readme update - new task.
2025-09-28 Added 7.5in e-paper display/driver docs
2026-01-02 Add ms_graph login
2026-01-02 Added arduino files
2026-01-02 Added config URL
2026-01-03 Arduino build config files added
2026-01-03 Added UV config. ms_graph converted to use TOML instead of dotenv.
2026-01-03 MSAL version of calendar access created
2026-01-03 Venv updates
2026-01-03 Python warnings cleanups
2026-01-03 Rename methods for consistency
2026-01-03 Deprecated old version of Outlook accessor. Keeping as some functionality needs to be ported later.
2026-01-03 Calling MSAL version of outlook access
2026-01-03 Update deprecated nicegui method
2026-01-03 missed file on last commit
2026-01-03 another missed file
2026-01-03 Added TRMNL config & use it.
2026-01-03 Broke Outlook object out of plugin file
2026-01-03 Minor updates reqd to gen an image
2026-01-03 TRMLN size image now being generated.
2026-01-04 Locked Pillow down to 11.3. 12.1 was not printing text properly
2026-01-04 Image roughly working
2026-01-04 Specify build output path
2026-01-04 Changes to start talking to server
2026-01-04 Rotate screen
2026-01-04 Arduino buld dir specified.
2026-01-04 Removed TEST message
2026-01-04 Another update due to lib changes
2026-01-04 Font update for non-anti-aliased screen
2026-01-04 TRMNL images now saved as 1-bit images
2026-01-04 Weather icon render updates
2026-01-04 Bold font added
2026-01-04 SVG rendering improvement.
2026-01-04 Remove unneeded params
2026-01-04 Battery status rendering updates
2026-01-04 Default devices when queried
2026-01-04 Default device db entries.
2026-01-04 Default db entry update
2026-01-04 Fixed default device entry gen.
2026-01-04 Device state string handling update
2026-01-04 Device state post working
2026-01-04 Abstracted read fcn
2026-01-04 Serial conditinally written. Now runs disconnected.
2026-01-19 Eliminate recursive call
2026-01-19 Readme update
2026-01-19 Move port
2026-01-19 Add path for dev.
2026-01-19 E-display goes straight to image.
2026-01-23 To do updates
2026-01-23 DB __main__ updates
2026-01-24 Skip enumerating events if none.
2026-01-24 Fix Outlook calendar timezone handling for Pacific time
    - Add timezone-aware datetime support using ZoneInfo
    - Set MS Graph API timezone preference to Pacific Standard Time
    - Ensures calendar events are queried correctly in local timezone
    - Fixes issue where events were not returned due to timezone mismatch
2026-01-25 Auto-detect system timezone for Outlook calendar queries
    - Replace hardcoded Pacific timezone with automatic system timezone detection
    - Add get_windows_timezone() helper to map IANA to Windows timezone names
    - Add fallback mappings for common timezone abbreviations (PST, EST, etc.)
    - Convert datetime queries to UTC format for MS Graph API compatibility
    - Improves portability across different timezone environments
2026-01-25 Fix Outlook calendar event rendering
    - Fix timezone comparison bug in CalendarBase.upcoming property that was
    preventing events from being filtered correctly. The code was removing
    timezone info from 'now' but comparing it to timezone-aware event times.
    - Use absolute paths for MS auth and token cache files based on module
    location instead of relative paths that only worked in plugins directory.
    - Add authentication error handling and logging to calendar renderer to
2026-01-25 Add diagonal hatching to calendar event boxes for E-ink display
    - Add 45-degree diagonal lines inside event boxes to indicate busy time
    - Add white background behind event text to keep text readable
    - Position text to avoid obscuring event box outline
    - Optimize visual clarity for black and white E-ink display
2026-01-25 Update inside temp rendering
2026-01-25 Center battery SoC text.
2026-01-25 Refactor all-day event rendering to display above time grid
    - Display all-day events as comma-separated list on same line as temperature
    - All-day events are left-justified, temperature remains right-justified
    - Text wraps appropriately to avoid overlap with temperature field
    - Filter all-day events from time grid display to show only timed events
    - Improve vertical spacing calculations for multi-line all-day event lists
2026-01-25 To-do list update
2026-01-25 Add battery voltage tracking and monitoring
    - Add battery_voltage field to DeviceState model with default -1.0
    - Update Arduino to send battery voltage instead of calculated SoC
    - Add battery_voltage_to_soc() function to convert voltage to percentage on server
    - Update state POST endpoint to accept battery_voltage and calculate SoC
    - Remove unused readBatterySoC() function from Arduino code
    - Support both legacy battery field and new battery_voltage field for backward compatibility
2026-01-25 Fix all-day event handling and consolidate end time adjustment logic
    - Move all-day event end time adjustment to EventBase constructor
    - Adjust end time by subtracting 1 day and setting to 23:59:59
    - Remove duplicate adjustment logic from calendar_google.py
    - Update renderer to use cal.upcoming instead of cal.events
    - Add debug statements in calendar_outlook_msal.py
2026-01-25 Display device battery voltage
2026-01-25 Handle temperature not in post payload
2026-01-25 MQTT tempreature not required
2026-01-25 Send device state over MQTT instead of HTTP post payload
2026-01-25 Fix bad AI import
2026-01-25 fix missed file save
2026-01-26 Captured additionals XIAO documentation
2026-01-26 Mechanical design initial
2026-02-01 Final fabrication updates to mechanicals
2026-02-02 Shift temperature display left a bit
2026-02-02 Add small bottom margin to keep text from being obscured by frame
2026-02-02 Added AI instructions file.
2026-02-02 move instructions file
2026-02-02 AI instructions updated for this project.
2026-02-02 MQTT class to listen for temperature messages.
2026-02-02 Use MQTT listener to capture temperature from other device and display that.
2026-02-06 Handle event fetch pagination in Outlook MSAL.
2026-02-06 Tweak text background
2026-02-17 Battery graph added.
